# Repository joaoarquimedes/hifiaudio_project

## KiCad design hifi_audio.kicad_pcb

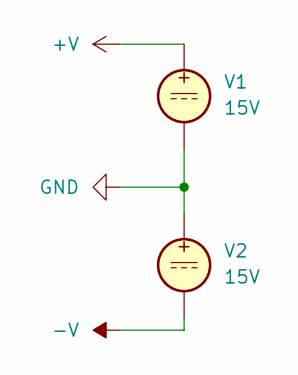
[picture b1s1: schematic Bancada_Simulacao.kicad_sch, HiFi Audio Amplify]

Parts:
V1, V2: 15V

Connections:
unnamed: V1.2, V2.1

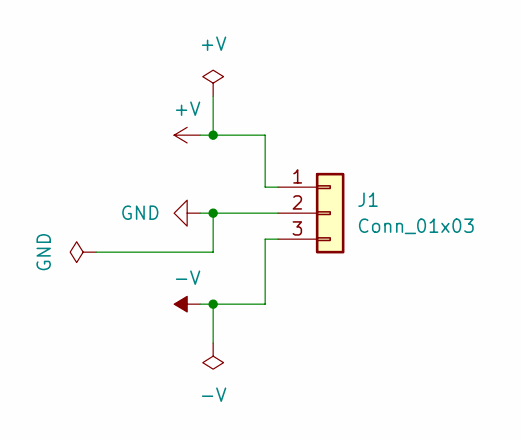
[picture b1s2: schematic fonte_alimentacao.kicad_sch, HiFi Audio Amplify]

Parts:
J1: Conn_01x03; JST_XH_B3B-XH-A_1x03_P2.50mm_Vertical

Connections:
+V: J1.1; also elsewhere on the board
-V: J1.3; also elsewhere on the board
GND: J1.2; also elsewhere on the board

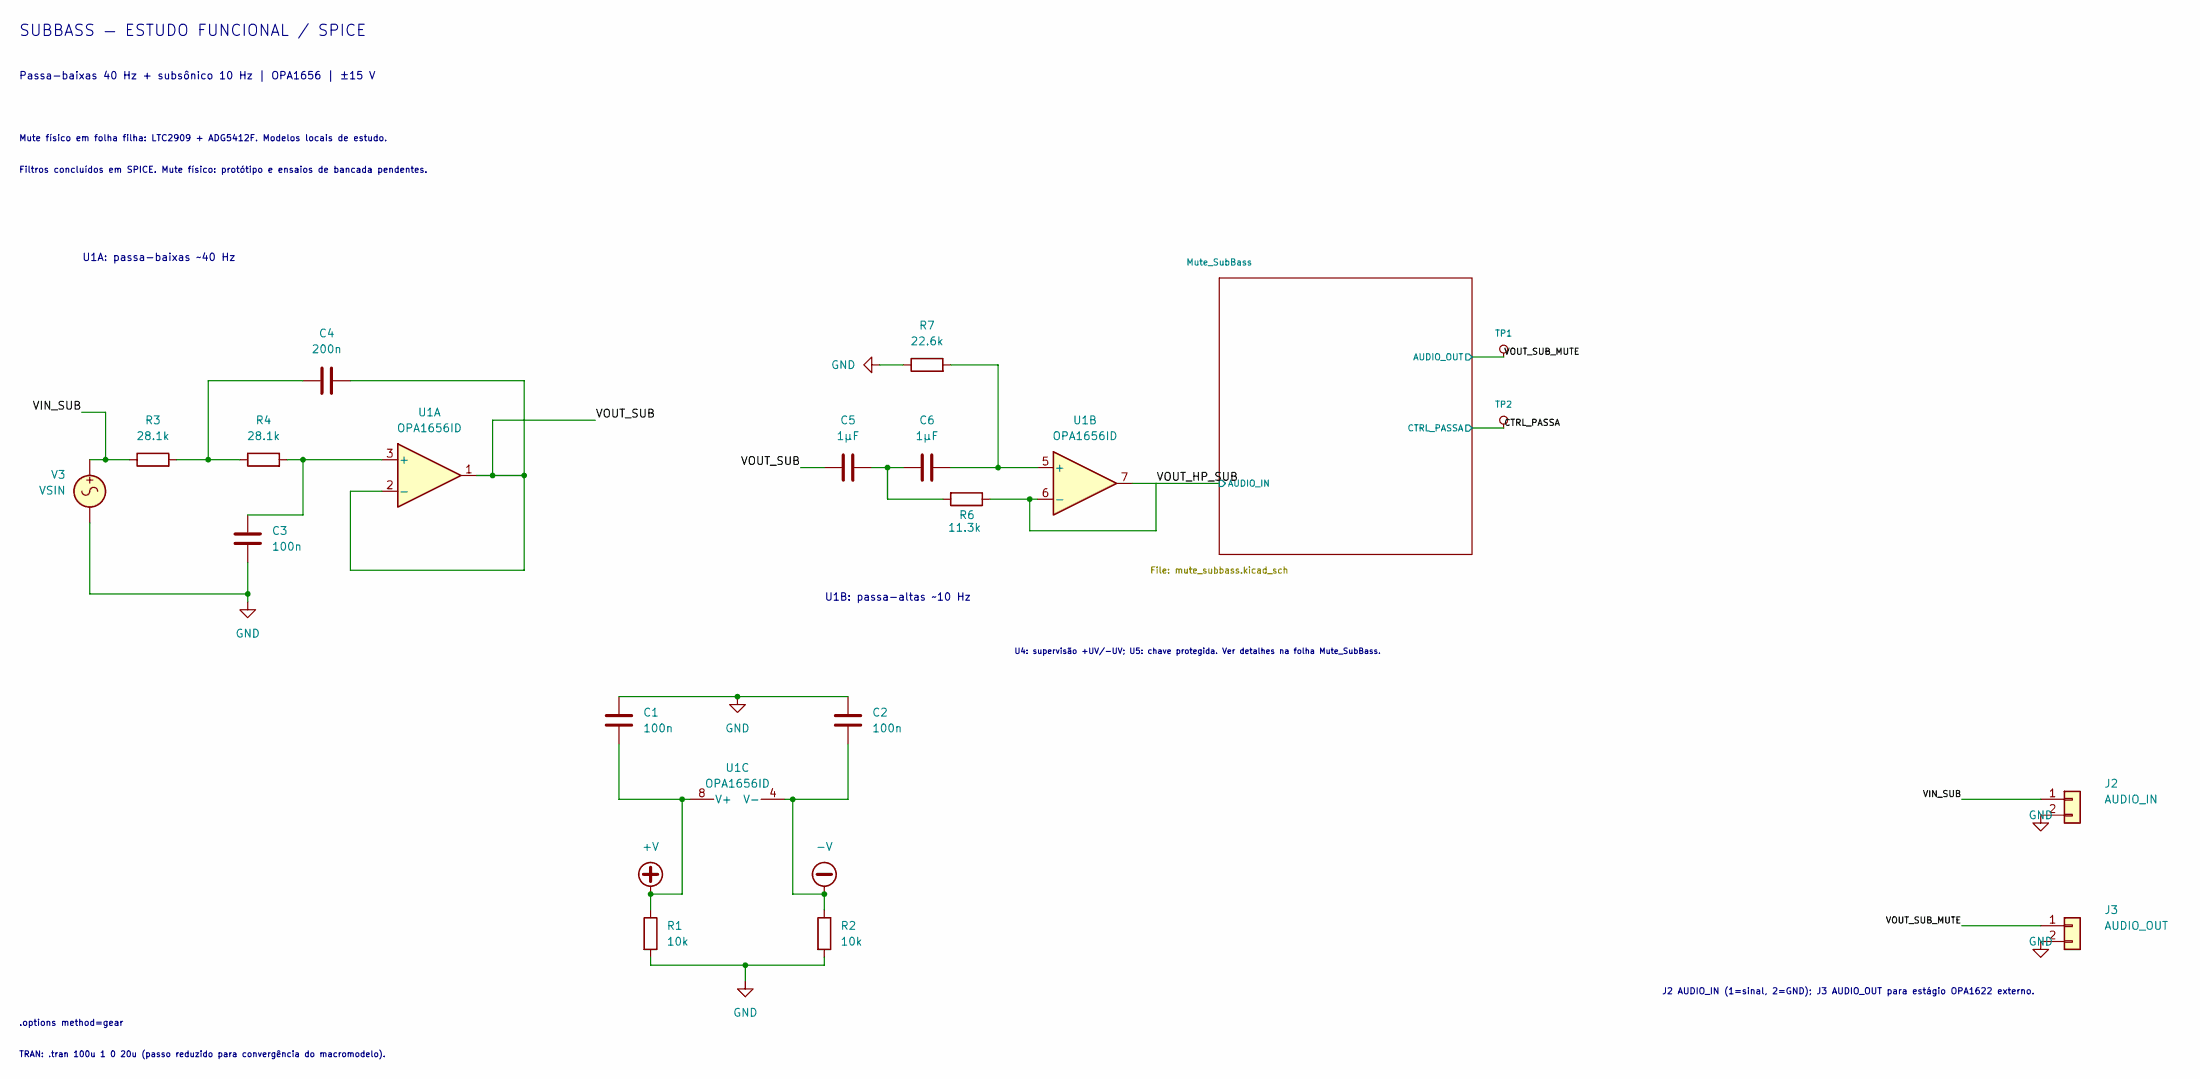
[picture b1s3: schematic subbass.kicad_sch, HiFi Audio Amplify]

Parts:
C1, C2, C3: 100n; C_0805_2012Metric
C4: 200n; C_0805_2012Metric
C5, C6: 1µF; C_1206_3216Metric
J2: AUDIO_IN; JST_XH_B2B-XH-A_1x02_P2.50mm_Vertical
J3: AUDIO_OUT; JST_XH_B2B-XH-A_1x02_P2.50mm_Vertical
R1, R2: 10k; R_0805_2012Metric
R3, R4: 28.1k; R_0805_2012Metric
R6: 11.3k; R_0805_2012Metric
R7: 22.6k; R_0805_2012Metric
TP1, TP2: TestPoint; TestPoint_Pad_D1.5mm
U1: OPA1656ID; SOIC-8_3.9x4.9mm_P1.27mm
V3: VSIN

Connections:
+V: C1.2, R1.1, U1.8 (V+); also elsewhere on the board
-V: C2.2, R2.1, U1.4 (V-); also elsewhere on the board
/subbass/CTRL_PASSA: TP2.1; also elsewhere on the board
/subbass/VIN_SUB: J2.1, R3.1, V3.1
/subbass/VOUT_HP_SUB: R6.1, U1.6 (-), U1.7; also elsewhere on the board
/subbass/VOUT_SUB: C4.2, C5.1, U1.1, U1.2 (-)
/subbass/VOUT_SUB_MUTE: J3.1, TP1.1; also elsewhere on the board
GND: C1.1, C2.1, C3.2, J2.2, J3.2, R1.2, R2.2, R7.1, V3.2; also elsewhere on the board
unnamed: C4.1, R3.2, R4.1
unnamed: C5.2, C6.1, R6.2
unnamed: C3.1, R4.2, U1.3 (+)
unnamed: C6.2, R7.2, U1.5 (+)

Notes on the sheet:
SUBBASS — ESTUDO FUNCIONAL / SPICE
Passa-baixas 40 Hz + subsônico 10 Hz | OPA1656 | ±15 V
U1A: passa-baixas ~40 Hz
U1B: passa-altas ~10 Hz
.options method=gear
TRAN: .tran 100u 1 0 20u (passo reduzido para convergência do macromodelo).
Mute físico em folha filha: LTC2909 + ADG5412F. Modelos locais de estudo.
Filtros concluídos em SPICE. Mute físico: protótipo e ensaios de bancada pendentes.
U4: supervisão +UV/-UV; U5: chave protegida. Ver detalhes na folha Mute_SubBass.
J2 AUDIO_IN (1=sinal, 2=GND); J3 AUDIO_OUT para estágio OPA1622 externo.

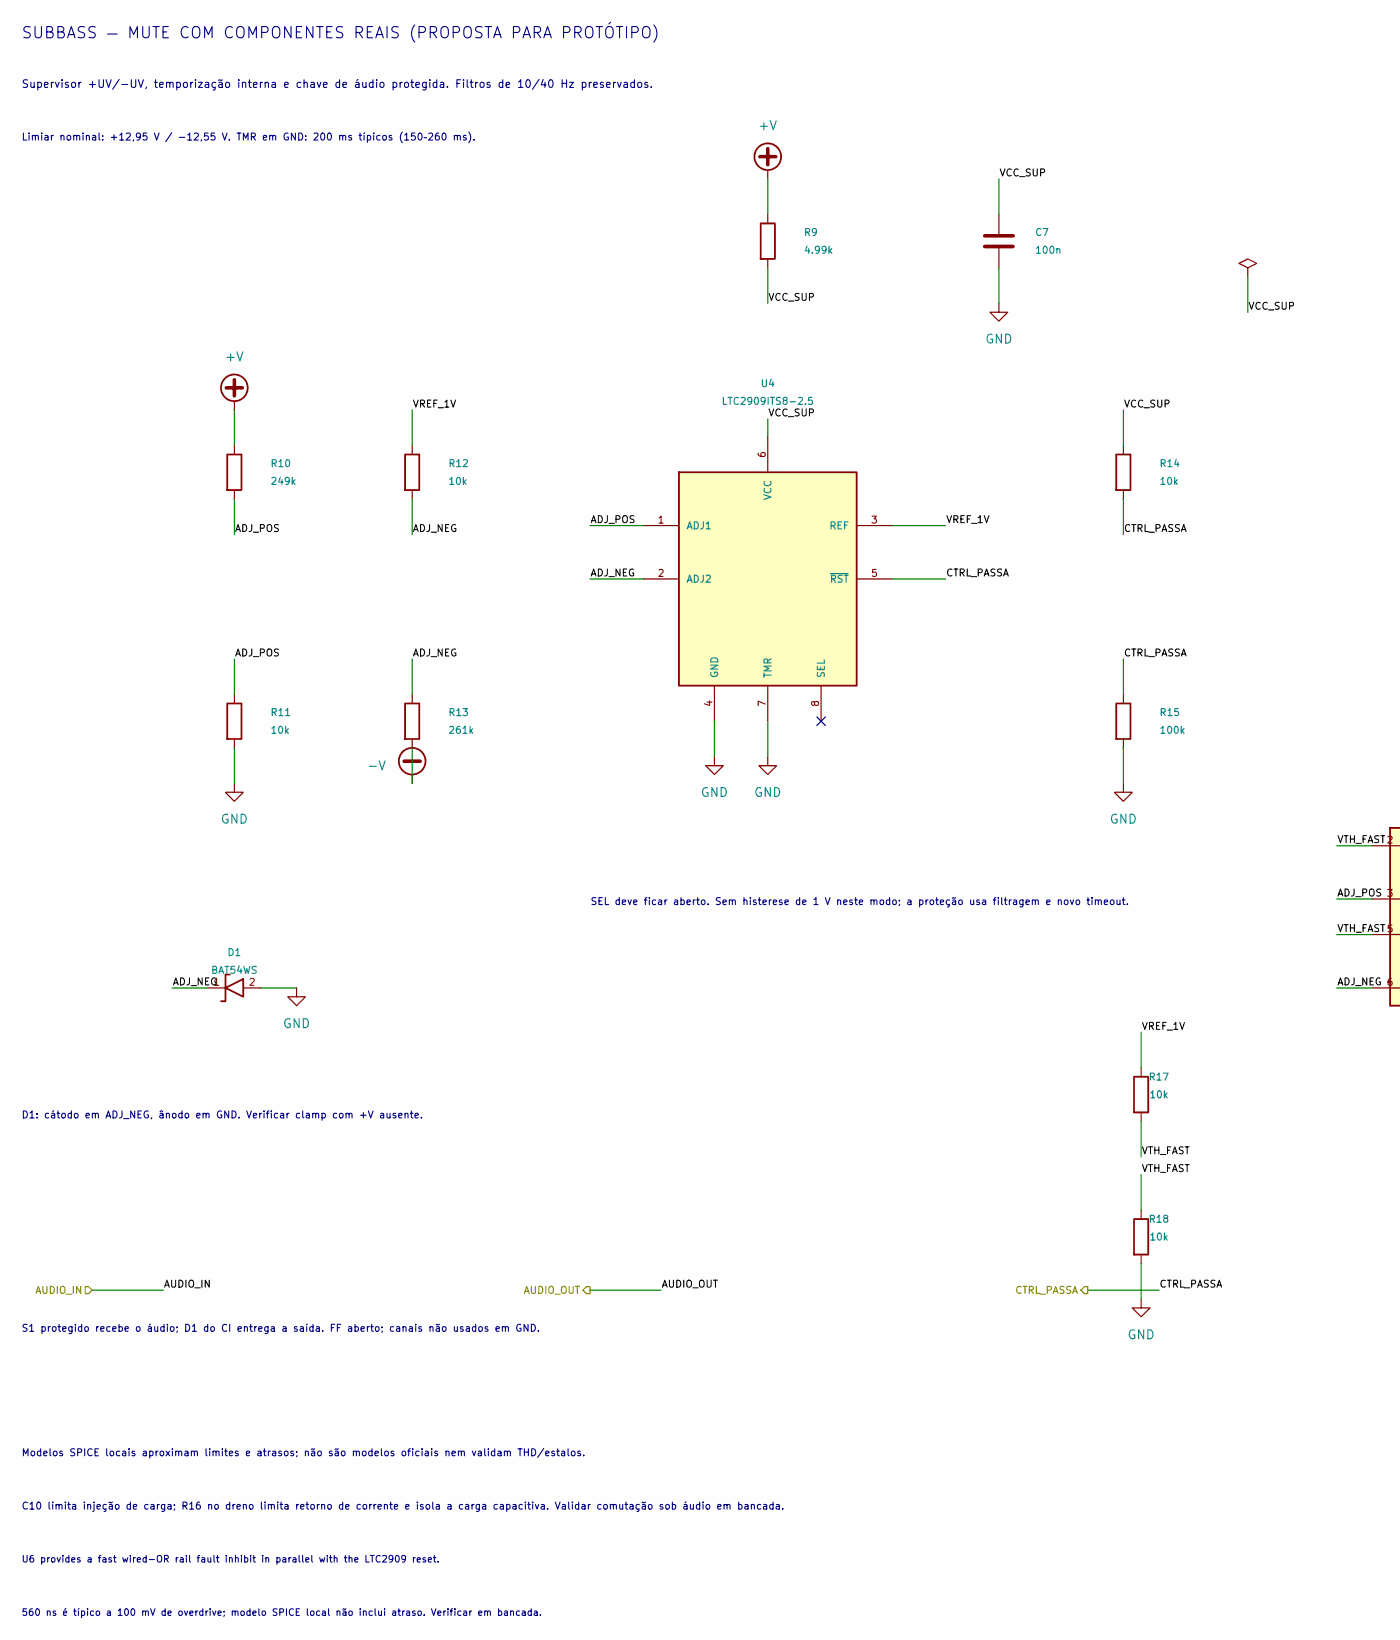
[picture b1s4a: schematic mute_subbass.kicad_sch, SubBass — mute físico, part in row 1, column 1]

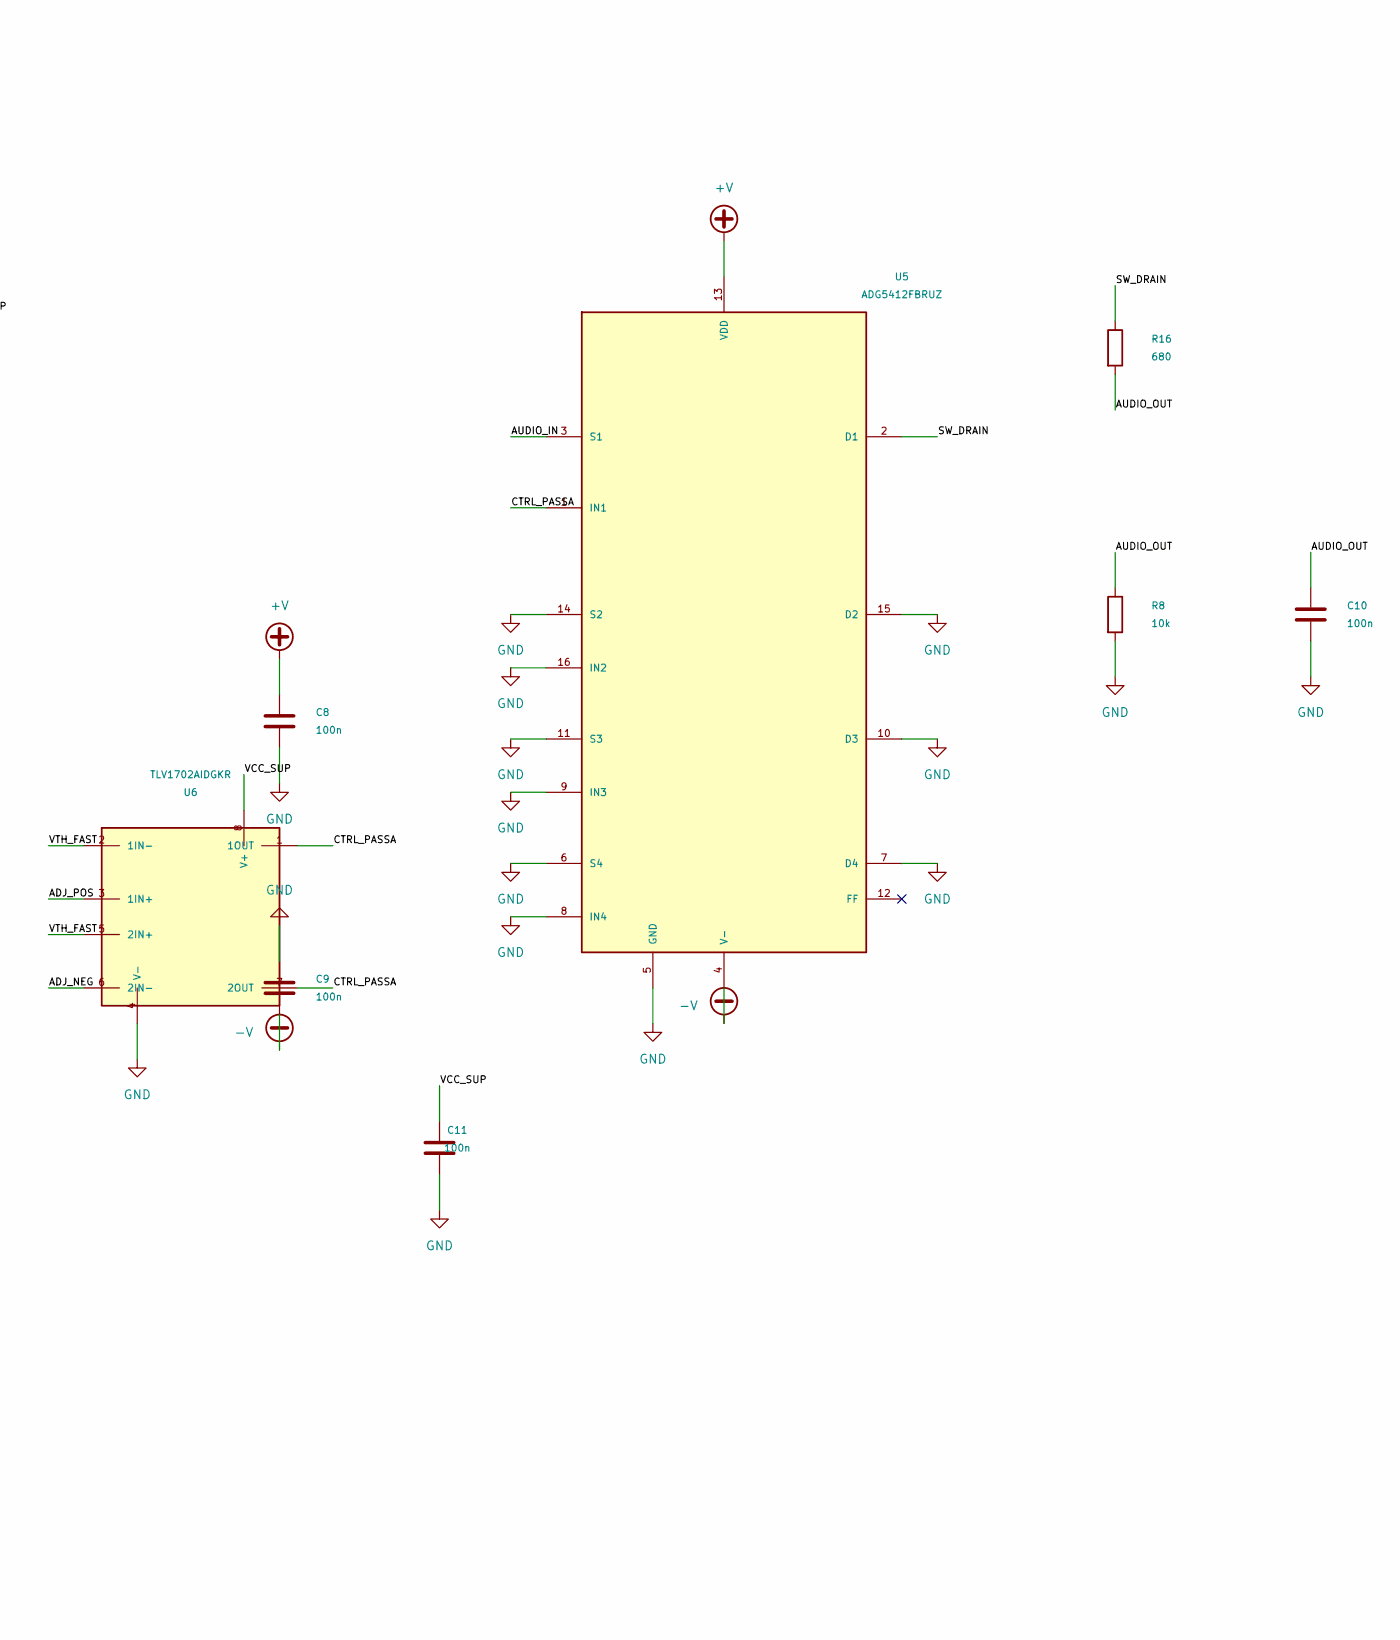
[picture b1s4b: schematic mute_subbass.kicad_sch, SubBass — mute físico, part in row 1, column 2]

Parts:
C7, C8, C9: 100n; C_0805_2012Metric; Voltage 50V; Tolerance 10%
C10: 100n; C_1206_3216Metric; Voltage 50V; Tolerance 5%
C11: 100n; C_0805_2012Metric; Voltage 50V; MPN GRM21BR71H104KA01L
D1: BAT54WS; D_SOD-323; MPN BAT54WS-7-F
R8, R14: 10k; R_0805_2012Metric; Tolerance 1%
R9: 4.99k; R_0805_2012Metric; Tolerance 0.1%
R10: 249k; R_0805_2012Metric; Tolerance 0.1%
R11, R12: 10k; R_0805_2012Metric; Tolerance 0.1%
R13: 261k; R_0805_2012Metric; Tolerance 0.1%
R15: 100k; R_0805_2012Metric; Tolerance 1%
R16: 680; R_1206_3216Metric; Tolerance 1%
R17, R18: 10k; R_0805_2012Metric; Tolerance 1%; MPN CRCW080510K0FKEA
U4: LTC2909ITS8-2.5; SOT-23-8; MPN LTC2909ITS8-2.5#TRMPBF
U5: ADG5412FBRUZ; TSSOP-16_4.4x5mm_P0.65mm; MPN ADG5412FBRUZ
U6: TLV1702AIDGKR; VSSOP-8_2.3x2mm_P0.5mm; MPN TLV1702AIDGKR

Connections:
+V: C8.1, R9.1, R10.1, U5.13 (VDD); also elsewhere on the board
-V: C9.2, R13.2, U5.4 (V-); also elsewhere on the board
/subbass/CTRL_PASSA: R14.2, R15.1, U4.5 (~RST), U5.1 (IN1), U6.1 (1OUT), U6.7 (2OUT); also elsewhere on the board
/subbass/Mute_SubBass/ADJ_NEG: D1.1 (K), R12.2, R13.1, U4.2 (ADJ2), U6.6 (2IN-)
/subbass/Mute_SubBass/ADJ_POS: R10.2, R11.1, U4.1 (ADJ1), U6.3 (1IN+)
/subbass/Mute_SubBass/SW_DRAIN: R16.1, U5.2 (D1)
/subbass/Mute_SubBass/VCC_SUP: C7.1, C11.1, R9.2, R14.1, U4.6 (VCC), U6.8 (V+)
/subbass/Mute_SubBass/VREF_1V: R12.1, R17.1, U4.3 (REF)
/subbass/Mute_SubBass/VTH_FAST: R17.2, R18.1, U6.2 (1IN-), U6.5 (2IN+)
/subbass/VOUT_HP_SUB: U5.3 (S1); also elsewhere on the board
/subbass/VOUT_SUB_MUTE: C10.1, R8.1, R16.2; also elsewhere on the board
GND: C7.2, C8.2, C9.1, C10.2, C11.2, D1.2 (A), R8.2, R11.2, R15.2, R18.2, U4.4 (GND), U4.7 (TMR), U5.5 (GND), U5.6 (S4), U5.7 (D4), U5.8 (IN4), U5.9 (IN3), U5.10 (D3), U5.11 (S3), U5.14 (S2), U5.15 (D2), U5.16 (IN2), U6.4 (V-); also elsewhere on the board

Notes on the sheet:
SUBBASS — MUTE COM COMPONENTES REAIS (PROPOSTA PARA PROTÓTIPO)
Supervisor +UV/-UV, temporização interna e chave de áudio protegida. Filtros de 10/40 Hz preservados.
Limiar nominal: +12,95 V / −12,55 V. TMR em GND: 200 ms típicos (150–260 ms).
SEL deve ficar aberto. Sem histerese de 1 V neste modo; a proteção usa filtragem e novo timeout.
D1: cátodo em ADJ_NEG, ânodo em GND. Verificar clamp com +V ausente.
S1 protegido recebe o áudio; D1 do CI entrega a saída. FF aberto; canais não usados em GND.
Modelos SPICE locais aproximam limites e atrasos; não são modelos oficiais nem validam THD/estalos.
C10 limita injeção de carga; R16 no dreno limita retorno de corrente e isola a carga capacitiva. Validar comutação sob áudio em bancada.
U6 provides a fast wired-OR rail fault inhibit in parallel with the LTC2909 reset.
560 ns é típico a 100 mV de overdrive; modelo SPICE local não inclui atraso. Verificar em bancada.

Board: 2 copper layers, 42 parts (0 on the bottom side), 18 nets, no tracks yet.

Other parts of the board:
MH1, MH2, MH3, MH4: MountingHole_3.2mm_M3

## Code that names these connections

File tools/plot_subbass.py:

#!/usr/bin/env python3
# /// script
# requires-python = ">=3.10"
# dependencies = ["matplotlib>=3.8,<4"]
# ///
"""Plot a completed verify_subbass.py run: uv run tools/plot_subbass.py RUN_DIR."""
import argparse
import csv
import json
from pathlib import Path
import math
import matplotlib
matplotlib.use('Agg')
import matplotlib.pyplot as plt

p=argparse.ArgumentParser(description=__doc__)
p.add_argument('run_dir',type=Path)
p.add_argument('--output',type=Path,default=None)
a=p.parse_args();out=a.output or a.run_dir;out.mkdir(parents=True,exist_ok=True)
result=json.loads((a.run_dir/'results.json').read_text())
if result['status'] not in ['PASS','FUNCTIONAL_PASS_WITH_LIMITATIONS']:raise SystemExit('Refusing to plot an incomplete / failed run as approved')

def load(name):
    with (a.run_dir/(name+'.csv')).open() as f:
        rows=list(csv.DictReader(f))
    return {k:[float(r[k]) for r in rows] for k in rows[0]}
plt.rcParams.update({'font.size':10})
fig,ax=plt.subplots(5,1,figsize=(12,12),sharex=True,layout='constrained')
d=load('startup_shutdown');t=[x*1000 for x in d['time']]
fig.suptitle('SubBass — mute automático com supervisão dos dois trilhos\nHW2: modelos locais; comparador sem atraso temporal · não aprovado para fabricação',fontsize=14)
ax[0].plot(t,d['vp'],label='+V');ax[0].plot(t,d['vn'],label='−V');ax[0].set_ylabel('Trilhos (V)')
ax[1].plot(t,d['adj_pos'],label='ADJ1 (+V)');ax[1].plot(t,d['adj_neg'],label='ADJ2 (−V)');ax[1].axhline(.5,color='#777',ls=':',label='Limiar nominal 0,5 V');ax[1].set_ylabel('Sensores (V)')
ax[2].plot(t,d['ctrl'],label='CTRL_PASSA / RST',color='#b28400');ax[2].set_ylabel('Controle (V)')
ax[3].plot(t,d['before'],label='Antes de S1',color='#2875b8');ax[3].plot(t,d['after'],label='Após S1',color='#c43d3d');ax[3].set_ylabel('Áudio (V)')
ax[4].plot(t,[v*1e6 for v in d['after']],label='Após S1 — ampliado',color='#c43d3d');ax[4].set_ylabel('Áudio (µV)');ax[4].set_xlabel('Tempo (ms)')
for x in ax:x.grid(alpha=.25);x.legend(loc='upper right',ncol=3);x.set_xlim(0,1000);x.axvspan(309.14,611.87,color='#65b96e',alpha=.08)
fig.savefig(out/'mute_automatico.png',dpi=150)
plt.close(fig)
fig,axs=plt.subplots(3,1,figsize=(12,9),sharex=True,layout='constrained')
fig.suptitle('Mute automático — perda de um trilho durante passagem de áudio\nEntrada 20 Hz / 2,828 Vp, iniciada aos 150 ms; recuperação exige novo atraso',fontsize=13)
for name,color,label in [('positive_fault','#2674b8','Falha +V'),('negative_fault','#9a59a6','Falha −V')]:
 d=load(name);t=[x*1000 for x in d['time']]
 axs[0].plot(t,d['vp'] if name=='positive_fault' else d['vn'],label=label,color=color)
 axs[1].plot(t,d['ctrl'],label=label,color=color)
 axs[2].plot(t,d['after'],label=label,color=color,alpha=.8)
for ax in axs:ax.grid(alpha=.25);ax.legend(loc='upper right');ax.set_xlim(0,1000)
axs[0].set_ylabel('Trilho afetado (V)');axs[1].set_ylabel('CTRL_PASSA (V)');axs[2].set_ylabel('Após S1 (V)');axs[2].set_xlabel('Tempo (ms)')
fig.savefig(out/'falhas_trilhos.png',dpi=150);plt.close(fig)
fig,ax=plt.subplots(2,1,figsize=(11,8),sharex=True,layout='constrained')
fig.suptitle('SubBass — resposta AC da cascata e perda da chave\nAlimentação DC ±15 V; análise no ponto de operação energizado',fontsize=13)
for name,label in [('ac_10k','Carga 10 kΩ'),('ac_2k','Carga 2 kΩ')]:
 d=load(name);gain=[];phase=[]
 for ar,ai,vr,vi in zip(d['after_real'],d['after_imag'],d['vin_real'],d['vin_imag']):
  h=complex(ar,ai)/complex(vr,vi);gain.append(20*math.log10(abs(h)));phase.append(math.degrees(math.atan2(h.imag,h.real)))
 ax[0].semilogx(d['frequency'],gain,label=label);ax[1].semilogx(d['frequency'],phase,label=label)
for x in ax:x.grid(which='both',alpha=.2);x.legend();x.axvline(10,ls=':',color='#777');x.axvline(40,ls=':',color='#777')
ax[0].set_ylabel('Ganho (dB)');ax[1].set_ylabel('Fase (°)');ax[1].set_xlabel('Frequência (Hz)');ax[0].set_ylim(-65,3)
fig.savefig(out/'resposta_ac.png',dpi=150);plt.close(fig)
print(out)
